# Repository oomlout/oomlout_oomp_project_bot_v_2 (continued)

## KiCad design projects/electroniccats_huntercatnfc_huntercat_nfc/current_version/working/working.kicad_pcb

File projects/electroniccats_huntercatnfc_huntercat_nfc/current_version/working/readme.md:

# huntercatnfc
 
## summary 
* id: electroniccats_huntercatnfc_huntercat_nfc
* user: electroniccats
* name: huntercatnfc
* board: huntercat_nfc
* repo: https://github.com/ElectronicCats/HunterCatNFC
* src_file_repo_kicad_pcb: Hardware/HunterCat-NFC/HunterCat-NFC.kicad_pcb
* src_file_repo_kicad_pcb_link: https://github.com/ElectronicCats/HunterCatNFC/tree/main/Hardware/HunterCat-NFC/HunterCat-NFC.kicad_pcb
* src_file_repo_kicad_sch: Hardware/HunterCat-NFC/HunterCat-NFC.kicad_sch
* src_file_repo_kicad_sch_link: https://github.com/ElectronicCats/HunterCatNFC/tree/main/Hardware/HunterCat-NFC/HunterCat-NFC.kicad_sch

* src_file_repo_sch: Hardware/HunterCat-NFC/HunterCat-NFC.sch
* src_file_repo_sch_link: https://github.com/ElectronicCats/HunterCatNFC/tree/main/Hardware/HunterCat-NFC/HunterCat-NFC.sch
* full details link: https://github.com/oomlout/oomlout_oomp_project_bot_v_2/tree/main/projects/electroniccats_huntercatnfc_huntercat_nfc/current_version/working

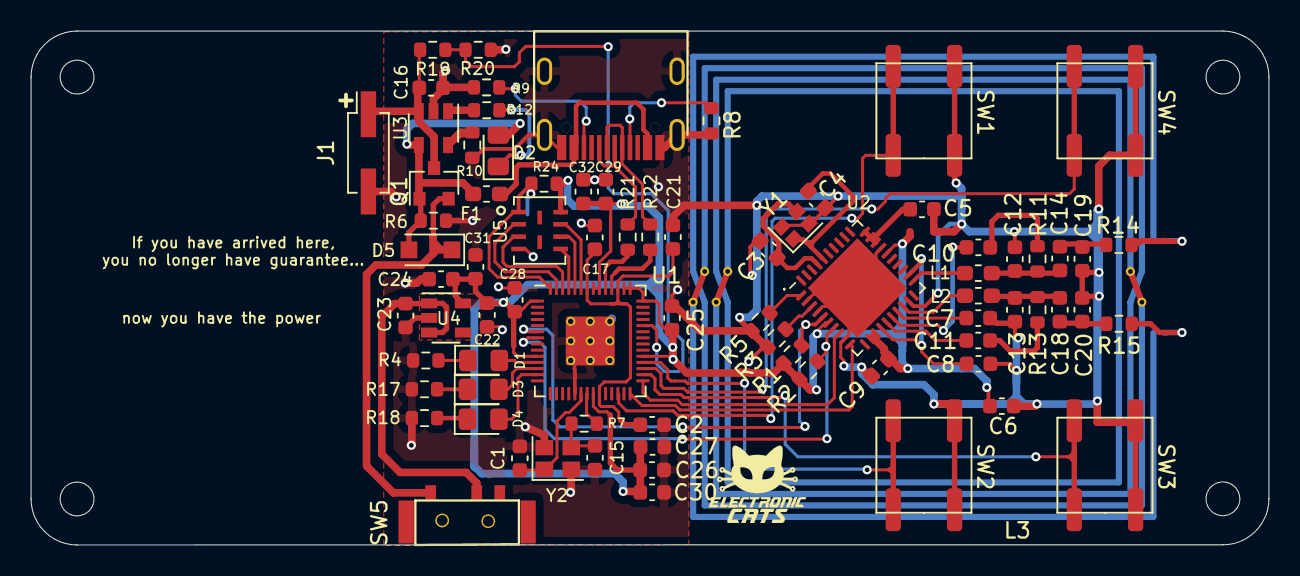
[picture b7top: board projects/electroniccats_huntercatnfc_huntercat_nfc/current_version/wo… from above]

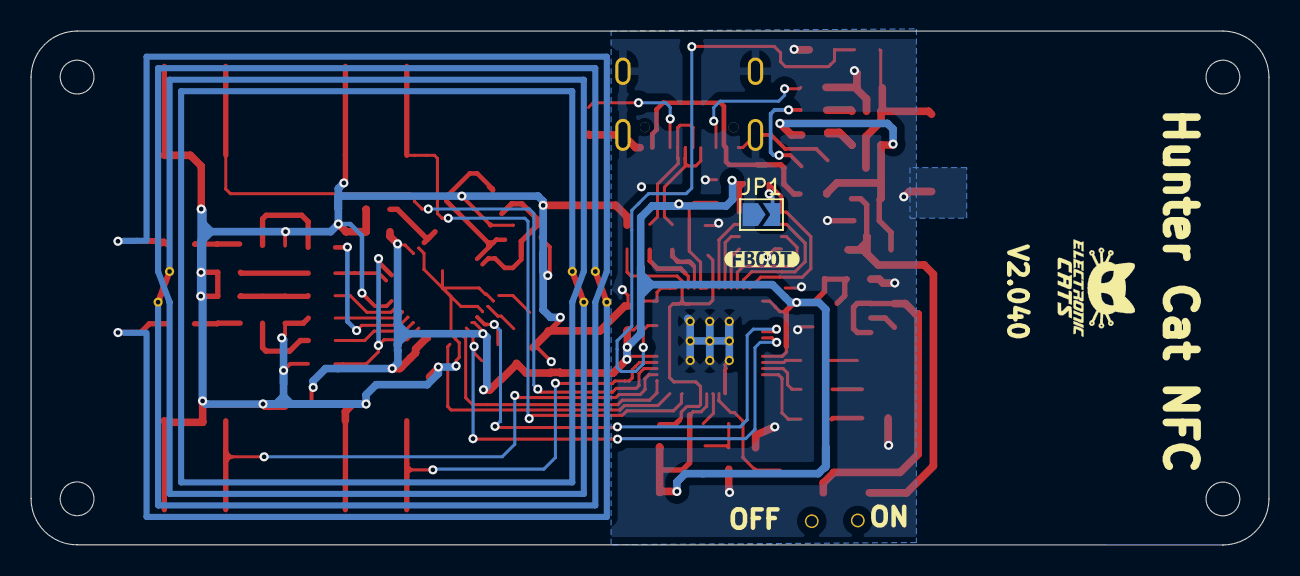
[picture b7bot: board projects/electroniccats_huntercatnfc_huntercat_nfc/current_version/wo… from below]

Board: 2 copper layers, 80.7 x 33.5 mm, 84 parts (3 on the bottom side), 60 nets.

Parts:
C1, C15: 27pF; C_0603_1608Metric
C2, C5, C6, C8, C22: 1uF; C_0603_1608Metric
C3, C4: 10pF; C_0603_1608Metric
C7, C9: 100nF; C_0603_1608Metric
C10, C11: 1nF/16V; C_0603_1608Metric
C12, C13: 680pF; C_0603_1608Metric
C14, C18: 100pF/50V; C_0603_1608Metric
C16, C23, C24: 10uF; C_0603_1608Metric
C17, C21, C25, C26, C27, C28, C29, C30, C31, C32: 0.1uF; C_0603_1608Metric
C19, C20: 120pF; C_0603_1608Metric
D1, D2, D3, D4: LED; LED_0805_2012Metric_Pad1.15x1.40mm_HandSolder
D5: MBR120; D_SOD-123F
F1: 0.5A; Fuse_0603_1608Metric_Pad1.05x0.95mm_HandSolder
H1, H2, H3, H4: MountingHole; MountingHole_2.2mm_M2
J1: Battery; PinSocket_2x01_P2.54mm_Vertical_SMD
JP1: BOOT; SolderJumper-2_P1.3mm_Open_TrianglePad1.0x1.5mm
L1, L2: 160nH; L_0603_1608Metric_Pad1.05x0.95mm_HandSolder
L3: L; NFC-antenna30.4x30.4mm
P1: USB_C_Plug_USB2.0; C393939
Q1: DMG3415U-7; SOT-23
R1, R2, R24: 10K; R_0603_1608Metric
R3, R5, R6, R19, R20: 100K; R_0603_1608Metric
R4, R17, R18: 330; R_0603_1608Metric
R7, R12: 1K; R_0603_1608Metric
R8, R9: 5k1; R_0603_1608Metric
R10: 4.7K; R_0603_1608Metric
R11, R13: 2k2; R_0603_1608Metric
R14, R15: 3.24R; R_0603_1608Metric
R21, R22: 27; R_0603_1608Metric
SW1: RESET; KSC941JLFS
SW2: GPIO; KSC941JLFS
SW3: GPIO1; KSC941JLFS
SW4: GPIO2; KSC941JLFS
SW5: ON; Micro_interruptor_SPDT
U1: RP2040; RP2040-QFN-56
U2: PN7150B0HN_C11002E-PN7150B0HN_C11002E; QFN-40-1EP_6x6mm_P0.5mm_EP4.6x4.6mm
U3: MCP73831-3-OT; SOT-23-5
U4: AP2112K-3.3; SOT-23-5
U5: W25Q16JV; W25Q16JVUUIQ
Y1: 27.12Mhz; Crystal_SMD_2016-4Pin_2.0x1.6mm
Y2: 12Mhz; Crystal_SMD_2520-4Pin_2.5x2.0mm
kibuzzard-62BD092C: G***; kibuzzard-62BD092C

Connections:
+1V2: C2.1, C17.1, C21.1, U1.23 (DVDD), U1.45 (VREG_VOUT), U1.50 (DVDD)
+3V3: C6.1, C9.1, C22.1, C24.1, C25.1, C26.1, C27.1, C28.1, C29.1, C30.1, C31.1, C32.1, R1.1, R2.1, R24.1, U1.1 (IOVDD), U1.10 (IOVDD), U1.22 (IOVDD), U1.33 (IOVDD), U1.42 (IOVDD), U1.43 (ADC_AVDD), U1.44 (VREG_IN), U1.48 (USB_VDD), U1.49 (IOVDD), U2.6 (VDD(PAD)), U2.12 (VBAT2), U2.13 (VBAT1), U2.26 (VBAT), U4.5 (VOUT), U5.8 (VCC)
+BATT: C16.1, J1.1, Q1.3 (D), R19.1, U3.3 (VBAT)
/ADR0: R5.1, U2.1 (I2CADR0)
/ADR1: R3.1, U2.3 (I2CADR1)
/B_ADC: R19.2, R20.1, U1.38 (GPIO26_ADC0)
/D+: P1.A6 (D+), R21.1
/D-: P1.A7 (D-), R22.1
/GPIO: SW4.2, U1.31 (GPIO20)
/GPIO1: SW2.2, U1.32 (GPIO21)
/GPIO2: SW3.2, U1.30 (GPIO19)
/IRQ: U1.29 (GPIO18), U2.8 (IRQ)
/LED1: D1.2 (A), U1.11 (GPIO8)
/LED2: D3.2 (A), U1.12 (GPIO9)
/LED3: D4.2 (A), U1.13 (GPIO10)
/QSPI_CS: JP1.2 (B), R24.2, U1.56 (QSPI_SS), U5.1 (~CS)
/QSPI_DATA0: U1.53 (QSPI_SD0), U5.5 (DI(IO0))
/QSPI_DATA1: U1.55 (QSPI_SD1), U5.2 (DO(IO1))
/QSPI_DATA2: U1.54 (QSPI_SD2), U5.3 (IO2)
/QSPI_DATA3: U1.51 (QSPI_SD3), U5.7 (IO3)
/QSPI_SCK: U1.52 (QSPI_SCLK), U5.6 (CLK)
/RD+: R21.2, U1.47 (USB_DP)
/RD-: R22.2, U1.46 (USB_DM)
/RST: SW1.2, U1.26 (RUN)
/RXN: C11.2, U2.15 (RXN)
/RXP: C10.2, U2.16 (RXP)
/SCL: R2.2, U1.7 (GPIO5), U2.7 (I2CSCL)
/SDA: R1.2, U1.6 (GPIO4), U2.5 (I2CSDA)
/TX1: L1.1, U2.21 (TX1)
/TX2: L2.2, U2.18 (TX2)
/VEN: U1.28 (GPIO17), U2.10 (VEN)
GND: C1.2, C2.2, C3.2, C4.2, C5.2, C6.2, C7.2, C8.2, C9.2, C12.2, C13.1, C15.2, C16.2, C17.2, C19.2, C20.1, C21.2, C22.2, C23.2, C24.2, C25.2, C26.2, C27.2, C28.2, C29.2, C30.2, C31.2, C32.2, J1.2, JP1.1 (A), P1.A1 (GND), R3.2, R4.2, R5.2, R6.2, R8.1, R9.1, R10.2, R17.2, R18.2, R20.2, SW1.1, SW2.1, SW3.1, SW4.1, U1.19 (TESTEN), U1.57 (GND), U2.2 (VSS), U2.4 (VSS(PAD)), U2.9 (VSS), U2.19 (VSS(TX)), U2.27 (VSS), U2.41 (VSS), U3.2 (VSS), U4.2 (GND), U5.4 (GND), Y1.2, Y1.4, Y2.2
unnamed: C1.1, U1.20 (XIN), Y2.1
unnamed: C3.1, U2.37 (NFC_CLK_XTAL2), Y1.3
unnamed: C4.1, U2.36 (NFC_CLK_XTAL1), Y1.1
unnamed: C5.1, U2.28 (VDDA), U2.29 (VDD), U2.30 (VDDD)
unnamed: C7.1, U2.17 (VDD(MID))
unnamed: C8.1, U2.14 (VDD(TX)), U2.22 (VDD(TX_IN))
unnamed: C10.1, R11.1
unnamed: C11.1, R13.2
unnamed: C12.1, C14.2, L1.2, R11.2
unnamed: C13.2, C18.2, L2.1, R13.1
unnamed: C14.1, C19.1, R14.2
unnamed: C15.1, R7.1, Y2.3
unnamed: C18.1, C20.2, R15.2
unnamed: C23.1, SW5.2 (B), U4.1 (VIN), U4.3 (EN)
unnamed: D1.1 (K), R4.1
unnamed: D2.1 (K), R12.2
unnamed: D3.1 (K), R17.1
unnamed: D4.1 (K), R18.1
unnamed: D5.1 (K), Q1.2 (S), SW5.1 (A)
unnamed: F1.1, P1.A4 (VBUS)
unnamed: L3.1, R14.1
unnamed: L3.2, R15.1
unnamed: P1.A5 (CC), R8.2
unnamed: P1.B5 (VCONN), R9.2
unnamed: R7.2, U1.21 (XOUT)
unnamed: R10.1, U3.5 (PROG)
unnamed: R12.1, U3.1 (STAT)
VBUS: D2.2 (A), D5.2 (A), F1.2, Q1.1 (G), R6.1, U3.4 (VDD)

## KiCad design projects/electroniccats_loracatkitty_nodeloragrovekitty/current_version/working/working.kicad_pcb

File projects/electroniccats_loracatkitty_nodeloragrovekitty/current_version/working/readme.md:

# loracatkitty
 
## summary 
* id: electroniccats_loracatkitty_nodeloragrovekitty
* user: electroniccats
* name: loracatkitty
* board: nodeloragrovekitty
* repo: https://github.com/ElectronicCats/LoRaCatKitty
* src_file_repo_kicad_pcb: NodeLoRaGroveKitty.kicad_pcb
* src_file_repo_kicad_pcb_link: https://github.com/ElectronicCats/LoRaCatKitty/tree/master/NodeLoRaGroveKitty.kicad_pcb

* src_file_repo_sch: NodeLoRaGroveKitty.sch
* src_file_repo_sch_link: https://github.com/ElectronicCats/LoRaCatKitty/tree/master/NodeLoRaGroveKitty.sch
* full details link: https://github.com/oomlout/oomlout_oomp_project_bot_v_2/tree/main/projects/electroniccats_loracatkitty_nodeloragrovekitty/current_version/working

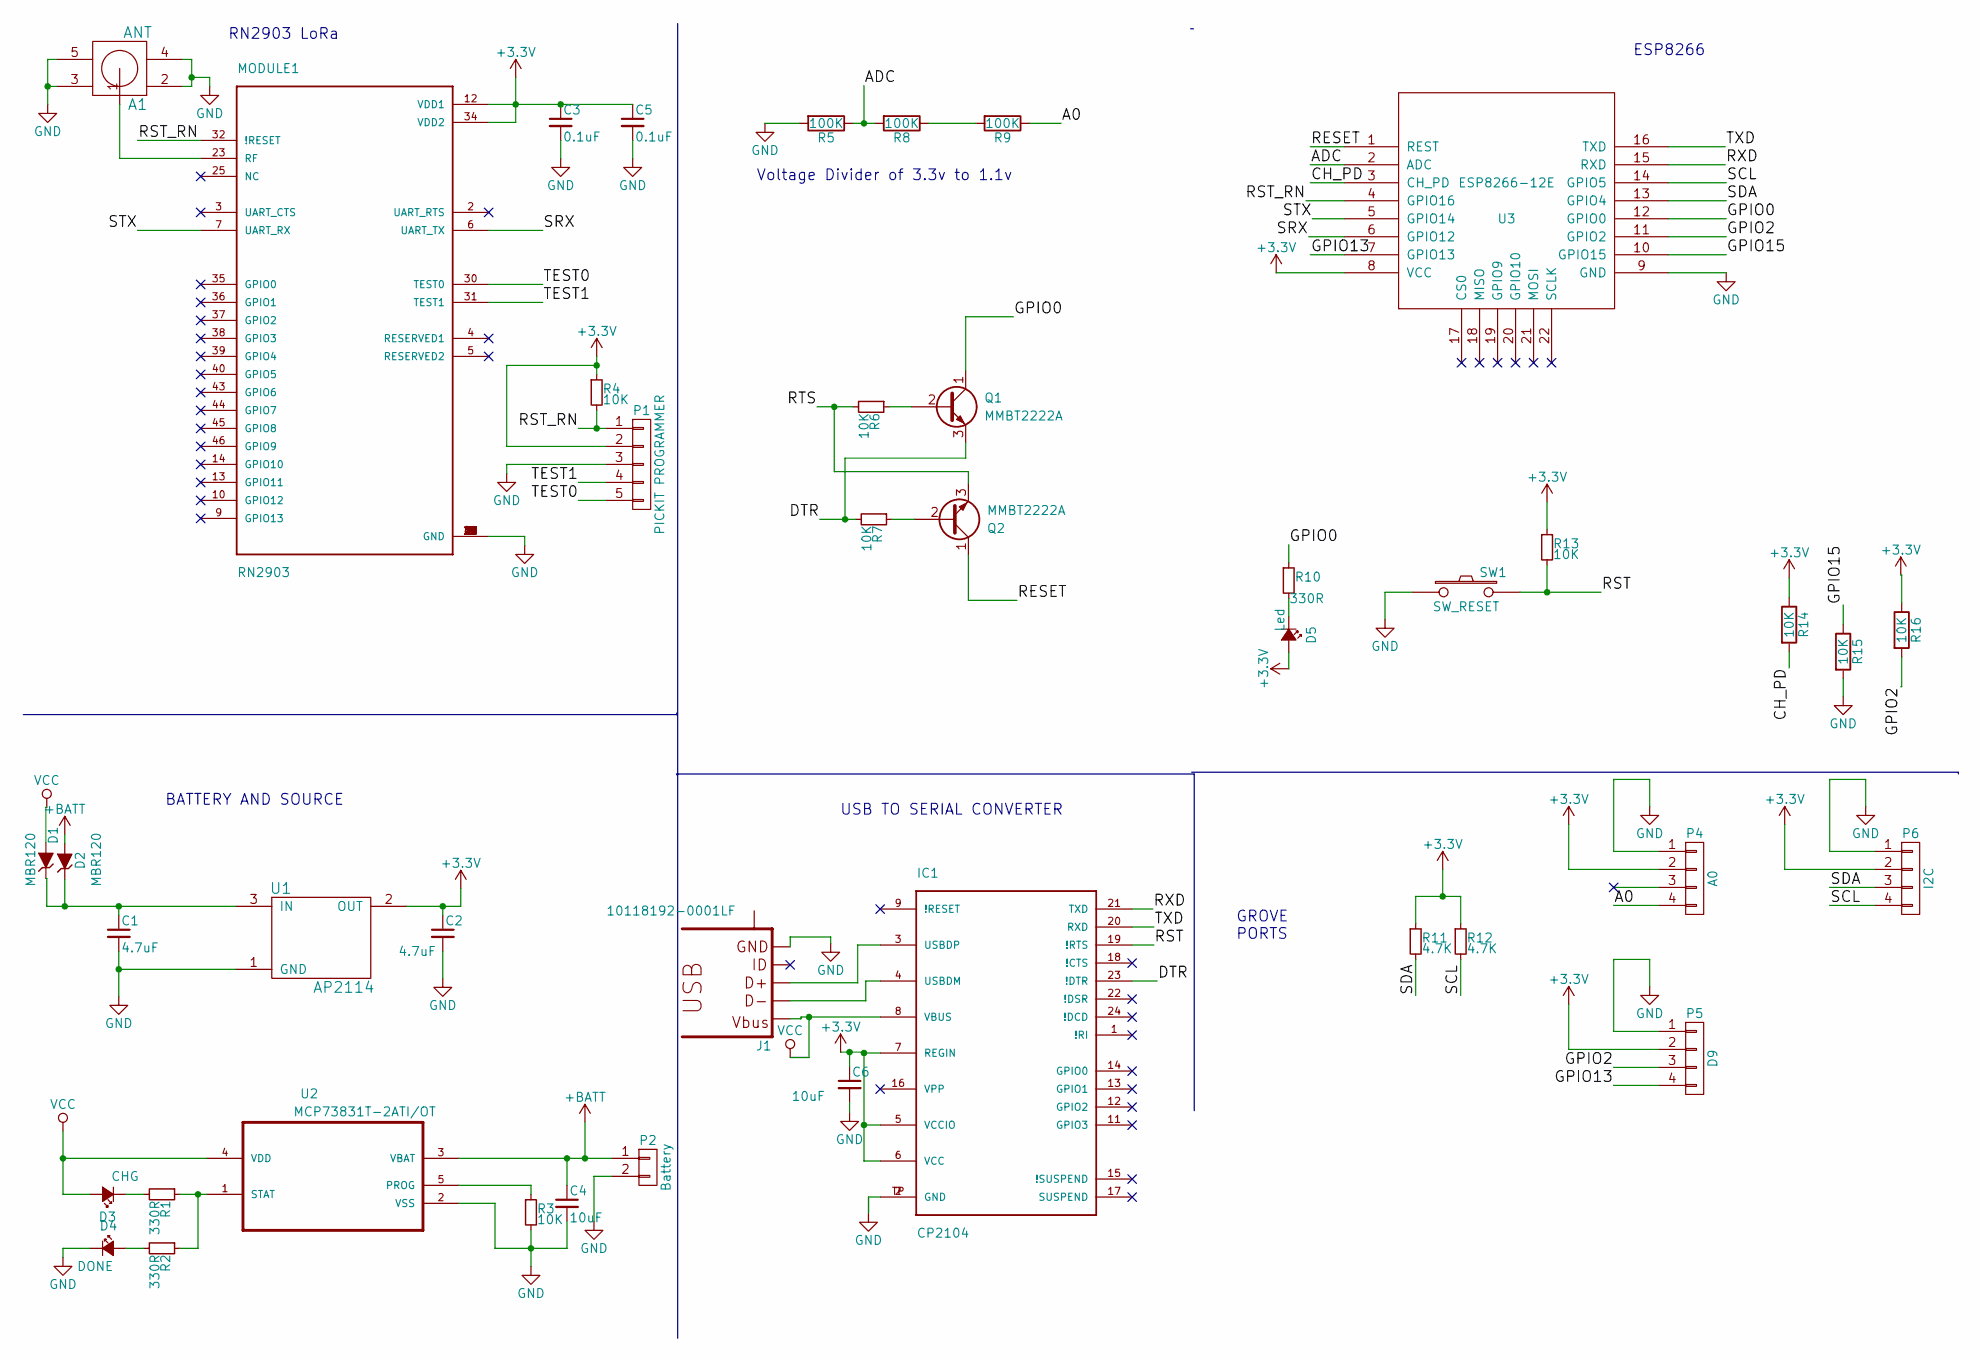
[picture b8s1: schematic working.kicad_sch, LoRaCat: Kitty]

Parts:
A1: ANT; SMA_Conn_Ant
C1, C2: 4.7uF; C_0805_HandSoldering
C3, C5: 0.1uF; C_0805_HandSoldering
C4, C6: 10uF; C_0805_HandSoldering
D1, D2: MBR120; D_SOD-123
D3: CHG; LED_0805
D4: DONE; LED_0805
D5: Led; LED_0805
IC1: CP2104; QFN-24_4x4mm_Pitch0.5mm_NoMask
J1: 10118192-0001LF
MODULE1: RN2903; RN2483
P1: PICKIT PROGRAMMER; Pin_Header_Straight_1x05_Pitch2.54mm
P2: Battery; panelmate_smd_2
P4: A0; JST_PH_S4B-PH-SM4-TB_04x2.00mm_Angled
P5: D9; JST_PH_S4B-PH-SM4-TB_04x2.00mm_Angled
P6: I2C; JST_PH_S4B-PH-SM4-TB_04x2.00mm_Angled
Q1, Q2: MMBT2222A; SOT-23
R1, R2, R10: 330R; R_0805_HandSoldering
R3, R4, R6, R7, R13, R14, R15, R16: 10K; R_0805_HandSoldering
R5, R8, R9: 100K; R_0805_HandSoldering
R11, R12: 4.7K; R_0805_HandSoldering
SW1: SW_RESET; SW_SPST_B3U-1000P
U1: AP2114; SOT-223-3Lead_TabPin2
U2: MCP73831T-2ATI/OT; SOT-23-5
U3: ESP8266-12E; ESP-12E

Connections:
+3V3: C2.1, C3.1, C5.1, C6.1, D5.2 (A), IC1.5 (VCCIO), IC1.6 (VCC), IC1.7 (REGIN), MODULE1.12 (VDD1), MODULE1.34 (VDD2), P1.2, P4.2, P5.2, P6.2, R4.1, R11.1, R12.1, R13.1, R14.1, R16.1, U1.2 (OUT), U3.8 (VCC)
+BATT: C4.1, D2.2 (A), P2.1, U2.3 (VBAT)
/A0: P4.4, R9.1
/ADC: R5.1, R8.2, U3.2 (ADC)
/CH_PD: R14.2, U3.3 (CH_PD)
/DTR: IC1.23 (!DTR), Q1.3 (E), R7.2
/GPIO0: Q1.1 (C), R10.1, U3.12 (GPIO0)
/GPIO2: P5.3, R16.2, U3.11 (GPIO2)
/GPIO13: P5.4, U3.7 (GPIO13)
/GPIO15: R15.1, U3.10 (GPIO15)
/RESET: Q2.1 (C), U3.1 (REST)
/RST: IC1.19 (!RTS), R13.2, SW1.2; also elsewhere on the board
/RST_RN: MODULE1.32 (!RESET), P1.1, R4.2, U3.4 (GPIO16)
/RTS: Q2.3 (E), R6.2
/RXD: IC1.21 (TXD), U3.15 (RXD)
/SCL: P6.4, R12.2, U3.14 (GPIO5)
/SDA: P6.3, R11.2, U3.13 (GPIO4)
/SRX: MODULE1.6 (UART_TX), U3.6 (GPIO12)
/STX: MODULE1.7 (UART_RX), U3.5 (GPIO14)
/TEST0: MODULE1.30 (TEST0), P1.5
/TEST1: MODULE1.31 (TEST1), P1.4
/TXD: IC1.20 (RXD), U3.16 (TXD)
GND: A1.2, A1.3, A1.4, A1.5, C1.2, C2.2, C3.2, C4.2, C5.2, C6.2, D4.1 (K), IC1.2 (GND), IC1.TP (GND), J1.5 (GND), MODULE1.1 (GND), MODULE1.8 (GND), MODULE1.11 (GND), MODULE1.20 (GND), MODULE1.21 (GND), MODULE1.22 (GND), MODULE1.24 (GND), MODULE1.26 (GND), MODULE1.27 (GND), MODULE1.28 (GND), MODULE1.33 (GND), MODULE1.41 (GND), MODULE1.47 (GND), P1.3, P2.2, P4.1, P5.1, P6.1, R3.2, R5.2, R15.2, SW1.1, U1.1 (GND), U2.2 (VSS), U3.9 (GND); also elsewhere on the board
unnamed: A1.1, MODULE1.23 (RF)
unnamed: C1.1, D1.1 (K), D2.1 (K), U1.3 (IN)
unnamed: D3.1 (K), R1.2
unnamed: D4.2 (A), R2.2
unnamed: D5.1 (K), R10.2
unnamed: IC1.3 (USBDP), J1.3 (D+)
unnamed: IC1.4 (USBDM), J1.2 (D-)
unnamed: J1.M1 (S), J1.M2 (S), J1.S1 (S), J1.S2 (S), J1.S3 (S), J1.S4 (S)
unnamed: Q1.2 (B), R6.1
unnamed: Q2.2 (B), R7.1
unnamed: R1.1, R2.1, U2.1 (STAT)
unnamed: R3.1, U2.5 (PROG)
unnamed: R8.1, R9.2
VCC: D1.2 (A), D3.2 (A), IC1.8 (VBUS), J1.1 (VBUS), U2.4 (VDD)

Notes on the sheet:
USB TO SERIAL CONVERTER
RN2903 LoRa
ESP8266
GROVE PORTS
Voltage Divider of 3.3v to 1.1v
BATTERY AND SOURCE

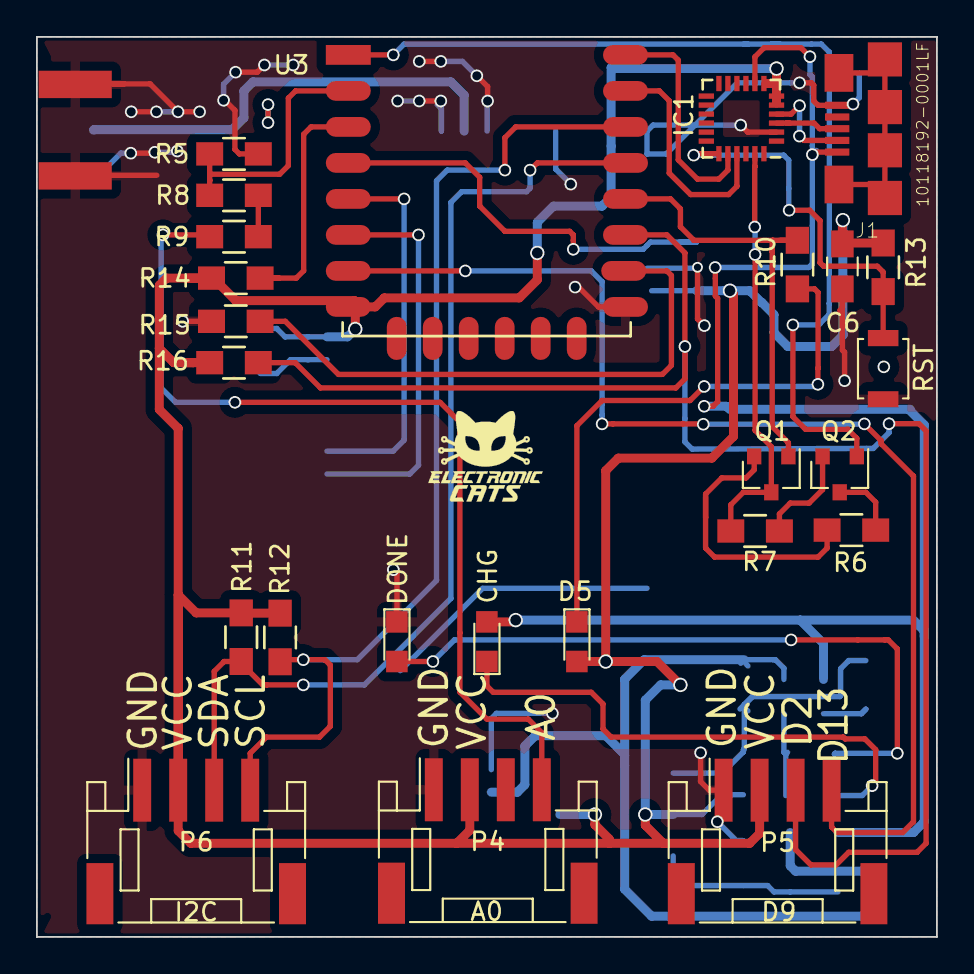
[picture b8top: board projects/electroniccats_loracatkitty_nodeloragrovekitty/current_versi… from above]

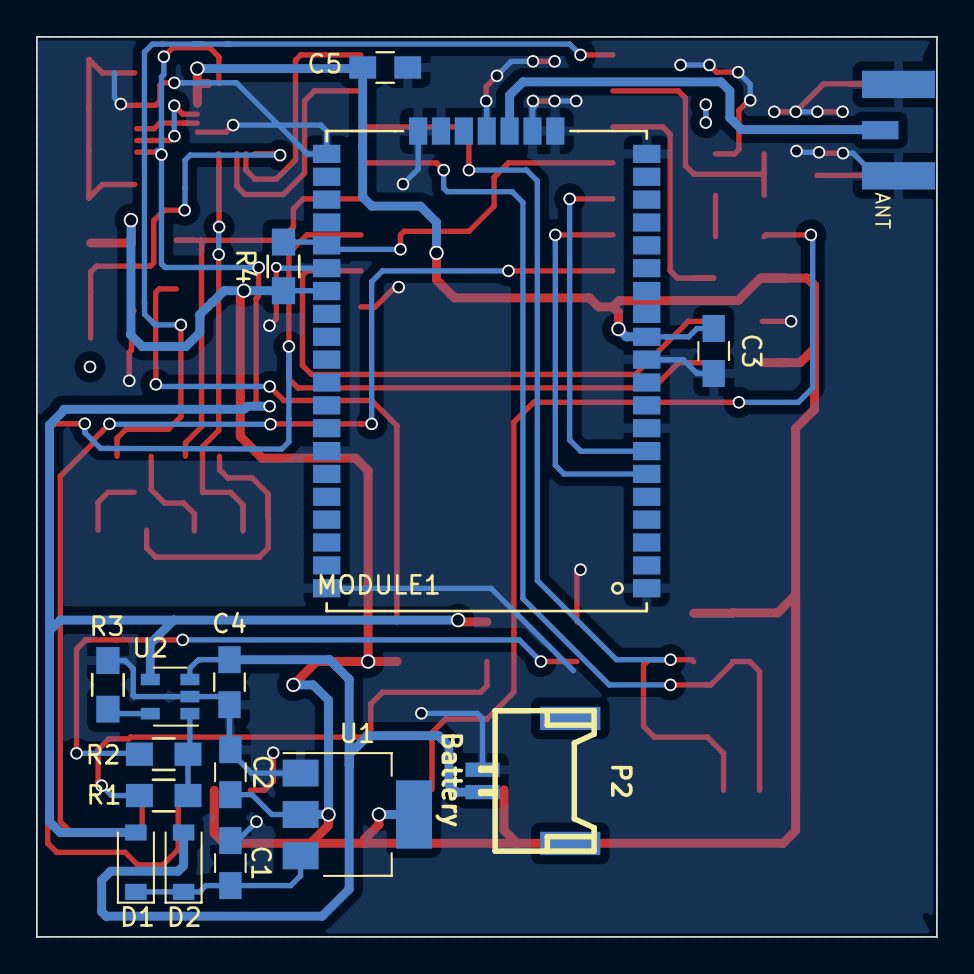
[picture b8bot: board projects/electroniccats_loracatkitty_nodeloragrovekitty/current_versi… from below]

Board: 2 copper layers, 50.0 x 50.0 mm, 41 parts (16 on the bottom side), 35 nets.

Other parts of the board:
RST: SW_RESET; SW_SPST_B3U-1000P

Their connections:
/RST: RST.2; also elsewhere on the board
GND: RST.1; also elsewhere on the board
